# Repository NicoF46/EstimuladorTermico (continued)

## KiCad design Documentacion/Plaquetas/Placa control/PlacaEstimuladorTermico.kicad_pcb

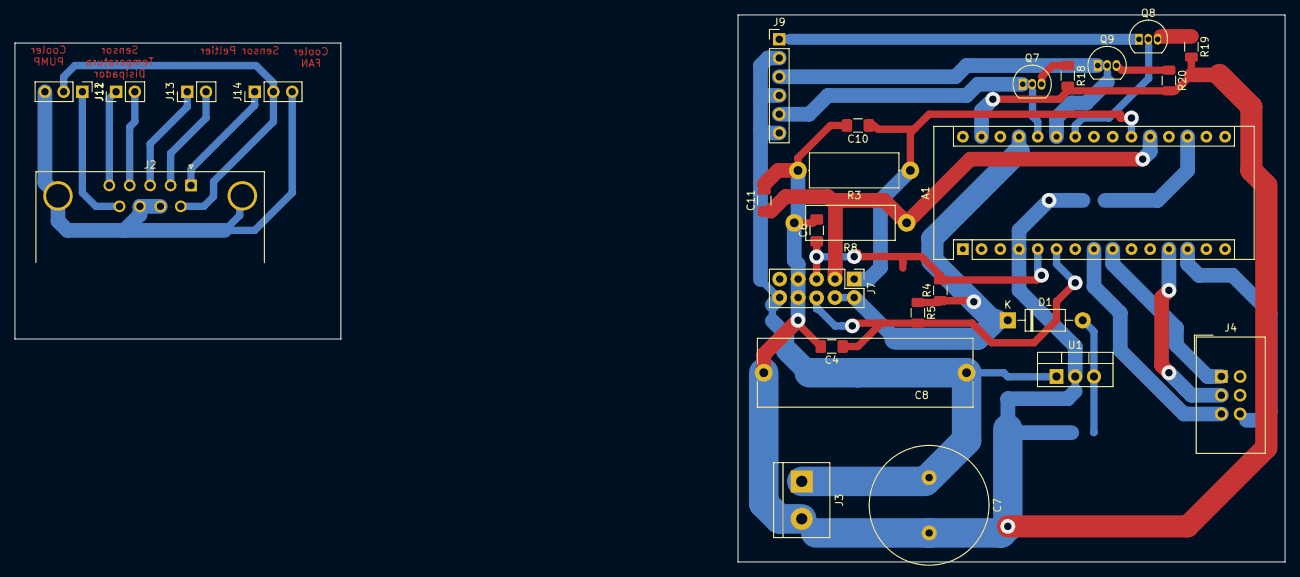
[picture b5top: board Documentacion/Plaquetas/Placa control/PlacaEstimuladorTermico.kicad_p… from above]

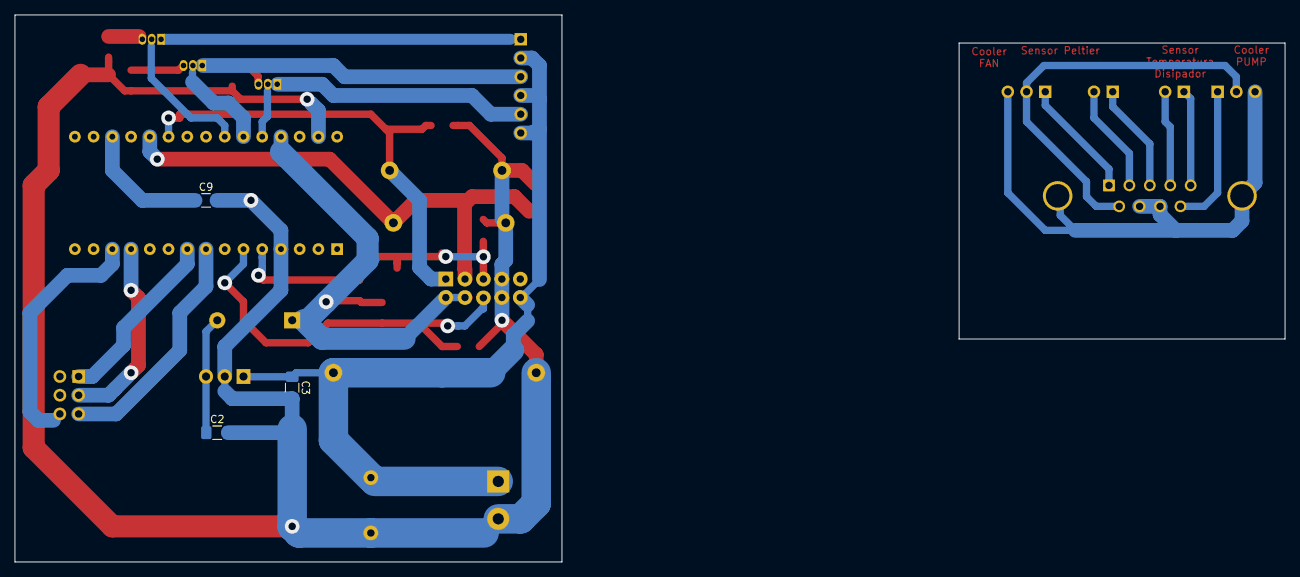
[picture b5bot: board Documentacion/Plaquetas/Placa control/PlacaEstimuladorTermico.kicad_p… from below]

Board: 2 copper layers, 74.2 x 74.2 mm, 31 parts (3 on the bottom side), 30 nets.

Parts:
A1: Arduino_Nano_v3.x; Arduino_Nano
C2, C9: 100n; C_1206_3216Metric_Pad1.42x1.75mm_HandSolder
C3: 330n; C_1206_3216Metric_Pad1.42x1.75mm_HandSolder
C4, C6: 2.2n; C_1206_3216Metric_Pad1.42x1.75mm_HandSolder
C7: 4700u; C_Radial_D16.0mm_H25.0mm_P7.50mm
C8: 4.7u; C_Rect_L29.0mm_W9.1mm_P27.50mm_MKT
C10, C11: 4.7n; C_1206_3216Metric_Pad1.42x1.75mm_HandSolder
D1: 1N4002; D_DO-41_SOD81_P10.16mm_Horizontal
J2: DB9_Female_MountingHoles; DSUB-9_Female_Horizontal_P2.77x2.84mm_EdgePinOffset7.70mm_H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
J3: Screw_Terminal_01x02; TerminalBlock_bornier-2_P5.08mm
J4: Conn_01x06_Male; IDC-Header_2x03_P2.54mm_Vertical
J7: Conn_02x05_Counter_Clockwise; PinHeader_2x05_P2.54mm_VerticalNico
J9: Conn_01x06_Male; PinHeader_1x06_P2.54mm_Vertical
J11, J14: Conn_01x03_Male; PinHeader_1x03_P2.54mm_Vertical
J12, J13: Conn_01x02_Male; PinHeader_1x02_P2.54mm_Vertical
Q7, Q8, Q9: BC548; TO-92_Inline
R3, R8: 10k; R_Axial_DIN0414_L11.9mm_D4.5mm_P15.24mm_Horizontal
R4, R5: 10k; R_1206_3216Metric
R18, R19, R20: 220; R_1206_3216Metric
U1: LM7805_TO220; TO-220-3_Vertical

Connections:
unnamed: A1.18, C9.1
unnamed: C2.1, D1.2, U1.3
unnamed: J9.1, Q8.1
unnamed: J9.3, Q9.1
unnamed: J9.5, Q7.1
unnamed: Q7.3, R18.1
unnamed: Q8.3, R19.1
unnamed: Q9.3, R20.1
PIN-CAUTION-LED-YELLOW: A1.25, Q9.2
PIN-READY-LED-GREEN: A1.24, Q8.2
PIN-WARNING-LED-RED: A1.26, Q7.2
PIN_SENSOR_TEMPERATURA_1: A1.20, C11.1, J7.2, R8.1
PIN_SENSOR_TEMPERATURA_2: A1.21, C10.1, J7.1, R3.1
PMOS_CALOR: A1.9, J4.1
PMOS_FRIO: A1.8, J4.5
PWM_CALOR: A1.12, J4.3
PWM_FRIO: A1.13, J4.6
REF_5: A1.27, D1.1, J7.9, J7.10, R4.1, R5.1
SENSOR_FAN: A1.6, C4.1, J7.8, R5.2
SENSOR_PUMP: A1.5, C6.1, J7.3, R4.2
VCC: C3.1, C7.1, C8.1, J3.1, J7.6, J9.2, J9.4, J9.6, U1.1
fan_1C: J2.6, J11.2, J14.2
fan_2: A1.4, A1.29, C2.2, C3.2, C4.2, C6.2, C7.2, C8.2, C9.2, C10.2, C11.2, J3.2, J7.4, J7.7, R3.2, R8.2, R18.2, R19.2, R20.2, U1.2
fan_2C: J2.7, J2.8, J11.3, J14.3
fan_sensor_C: J2.1, J14.1
pump_sensor_C: J2.9, J11.1
term_1_1C: J2.3, J13.1
term_1_2C: J2.2, J13.2
term_2_1C: J2.5, J12.1
term_2_2C: J2.4, J12.2

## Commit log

2019-04-15 Agrego carpeta para almacenar informacion util del peltier y un par de documentos en la misma
2019-04-15 Modifico Documentacion
2019-04-15 Agrego resumen de los umbrales de dolor y experimento de la mano plastica
2019-04-15 Cambio archivo a la carpeta correcta
2019-04-16 Agrego datasheet tec1-12715
2019-04-19 Agrego el codigo para sensar temperatura con el fabuloso termistor de mati
2019-04-20 quick example of how to plot real time data in python
2019-04-20 created a class Plotter to plot live data
2019-04-25 PWM y cambio a divisor resistivo
    Hecho el 24/04 en el LABI. Se cambio de medicion con puente de wheatstone a divisor resistivo con salida sobre resistencia fija.
    PWM en pin 6 controla la tension de gate del MOSFET
2019-05-07 Agrego documentacion
2019-05-08 added an autoscale option for the plotter
2019-05-10 finished the devices's client side in python
2019-05-10 Create LICENSE
2019-05-14 added a new csv with data
2019-05-14 added a csv_plotter
2019-05-14 Calculo del modelo térmico del Peltier
    Se agrego la documentación en la cual se basaron los cálculos para obtener el modelo térmico del Peltier junto con el código utilizado para obtener los parámetros.
2019-05-14 now the device transmit the pwm
2019-05-14 deleted senartemperaturacontermistor
2019-05-14 added a .gitignore file to ignore .pyc files
2019-05-14 deleted sensartemperaturacontermistor folder
2019-05-15 another test of the PID feedback
2019-05-15 Corrijo un bug
2019-05-15 Agrego los modos para que enfrie o caliente segun la referencia
2019-05-15 calibrated the pid
2019-05-17 Add files via upload
    archivo final miercoles 15/5
2019-05-19 started to modify the new circuit's firmware
2019-05-20 added a new mode selector
2019-05-20 changed the PID controller
2019-05-21 Now the device receive the temperature via serial interface
2019-05-21 updated requirements.txt
2019-05-22 started a cmd interface to send messages to the device
2019-05-22 added cmd package to requirements.txt
2019-05-22 finished the first version of the device
2019-08-20 fixing a bug when detecting the usb port
2019-08-27 Updated peltier model estimation
2019-09-06 Subo las simulaciones del informe correspondientes al circuito de control, me faltan las simulaciones del H bridge, la simulacion asi como la configure tarda un toque.
2019-09-06 Minor changes to peltier model estimation
2019-09-06 Agrego las 2 fotos
2019-09-29 Subo codigo del control en C
2019-10-01 Agrego jpg con el circuito de la placa de mati, cambie las resistencias de los mos de 100k a 10k, agregue el filtro LC y diodos flyback
2019-10-01 Simulación Circuito Protección
2019-10-02 Arreglo la transmision serie del arduino a la pc, me falta arreglar la de pc a arduino
2019-10-03 Resolvi el problema de la comunicacion, probe el codigo del pid funciona, tengo que ajustarlo y hacer la funcion de calibracion, dato a color el disipador con el filtro no calienta ni enfria como ant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
2019-10-05 Agrego el codigo para la calibracion
2019-10-14 Agrego el esquematico de la version 2 de la placa, me faltan algunos valores de resistencias y protecciones
2019-10-14 Agrego la resistencia en los mos
2019-10-17 Agrego el esquematico en png para mostrarlo hoy
2019-10-20 Deleting unnecesary files
2019-10-20 deleting .o and .hex files
2019-10-22 I selected the commercial components values and added to the schematic, I dont know if all the lines are connected correctly so please someone revise
2019-10-30 Add files via upload
    Actualizacion de esquematico: agregada proteccion de bateria
2019-11-01 Adding indicator lights and values to components
2019-11-02 I add all the footprints, the position of the high power mosfets is in acordance with a heatsink that I had
2019-11-04 I designed the pcb, it was my first try so please check every wire
2019-11-07 Add battery level to scheme, protection circuit correction & arranging
2019-11-07 add relay module symbol and footprint, modify mcp1407 symbol
    plus updates of these on the schematic
2019-11-09 solve kicad library issues
2019-11-28 Change pins of pwm and on off, adjusting pins in code to correct the problem
2019-12-03 DB9 board for peltier case
2019-12-03 DB9 board with bigger pads
2019-12-08 Correction of all the errors in the pcb
2019-12-09 Correction of pwm pins
2019-12-15 Modification of the main board, add of leds circuit and db9 board
2019-12-15 Add holes to the board
2019-12-15 Modifications in the schematic
2020-01-01 simplification of the dissipator temperature measurement circuit and simplification of code
2020-01-01 Add fuse and 7805 to supply the arduino nano
2020-01-05 Divide pcb in sectors based in functionality
2020-01-19 Updating firmware
2020-01-22 Creation of power pcb
2020-01-23 Possible layout
    Needs some rearenging.
    Added kiCAD backup files to ignore list
2020-01-24 Power PCB Routed
2020-01-29 Power PCB revised
    Minor changes in size and vias
2020-02-02 Power PCB footprints updated
2020-02-03 Power PCB retraced routes for new footprints
2020-02-03 Power PCB complete route retracing
2020-02-05 Power PCB revision - via size, signal connector pos and front pow traces
2020-02-07 Power PCB changed logic connector, widened traces, added mounting holes
2020-02-29 removing cache files
2020-02-29 removing kickad tables files
2020-02-29 removing kickad table files
2020-02-29 updating gitignore file
2020-03-01 Modifico el codigo para sintonizar el pid
2020-03-04 Protection PCB creation
    Needs choosing inverse polarity connection protection method
2020-03-05 Protection circuit on routed one sided 100x50mm board
    Relay outside board
    Possible improvements:
    - J3 moved left, decreases tracks length
    - U1 moved down, decreases tracks length, increases spacing between components
2020-03-07 removing *table files from gitignore
2020-03-18 Protection PCB footprint update, adjustable zenner ref set, pad resize
2020-03-20 Protection PCB widen tracks, connected unused opamp
    This is the final version. It was printed and etched
2020-03-31 Add control schematic
2020-05-10 changes in the schematic and pcb
2020-05-11 Addition of connetors on scheema and PCB
2020-05-11 PR requested schematic changes + removal of fan power supply conectors
    Fan power supply is going to be addressed by the protection circuit board
2020-05-11 git ignore
2020-05-13 Addition of buzzer, display and cold led
    Added a missing footprint to project
2020-05-14 Added fan supply circuitry, merged two 5v thermistor pin in one
2020-05-18 Added capacitor to buzzer transistor's base, changed 7805 diode side
    changed connector wire order,
    added proof of concept layout for single sided board,
    removed outdated and cache files
2020-05-19 Possible route design, swapped display connector pins
2020-05-19 Changed pump and fan sensor pins, routed accordingly, shrunk board size
2020-05-27 Possible design, swapped sda and scl connector pins
2020-05-27 changed buzzer to common collector mode
2020-06-06 Actualizacion del firmware por cambio en el hardware
2020-06-19 change pid and add commands for serial to work with flask
2020-07-04 adding multiple lines in a single plot
2020-07-04 updating data_acquisition script with the live_plot update
2020-07-06 upload changes calibration and pid
2020-07-12 Reorganising file composition
2020-07-17 adding the status library
2020-07-18 updating firmware with the new changes
2020-07-18 fixin a bad identation
2020-07-18 spliting status library into status and error library since some status and the NO_ERROR error state are compatibles
2020-07-18 adding a command to set errors
2020-07-18 Adding a code format option to the Makefile
2020-07-18 formatting code
2020-07-18 Fixing a missing path in the clean rule
2020-07-18 adding a script to setup the packages needed for development
2020-07-18 Installing a virtual environment with the python needs in the set up script
2020-07-19 Reading the temperature asynchronously
2020-07-28 adding a command to get the current pwm
2020-07-29 fixing a bug with the temperature used by reference
2020-08-08 Adding flags for each error
2020-08-10 code refactoring
2020-08-13 Adding a parity error check for usart transmision
2020-08-13 Adding sound alarm when an error is set
2020-08-17 Updating makefile to generate pygen files
2020-08-17 first aproach to a command generator based on a json file
2020-08-17 Autogenerating functions to red and transmit commands frames
2020-08-23 Fiing a bug with the function read_chung in commander.py
2020-08-30 Fixing a bug in Makefile. It rebuild the project if there are changes in .json files
2020-08-31 Removing .gen.c files with make clean
2020-08-31 adding a temperature module
2020-08-31 adding a power_board library
2020-08-31 declaring as const input variables
2020-08-31 removing old files
2020-09-01 removing duplicated variable in Makefile
2020-09-07 Refactoring controller functions and adding documentation to some funcionts
2020-09-07 updating data link
2020-09-07 Adding measures to compare thermistors in different locations
2020-09-10 adding a command that return the average temperature
2020-09-13 Adding stop command and fixig a bug where the live plot windows was always on top
2020-09-13 adding errors commands
2020-09-13 Swaping leds ports for the new board
2020-09-20 adding a starting routine to test leds and the buzzer
2020-09-20 Reducing the test duration
2020-09-20 Reducing even more the test duration
2020-10-13 Adding a keep alive that resets on each temperature_read command call
2020-10-16 Finishing the keep alive implementation
2020-10-17 first aproach to an error checker. Tachometer is not checked still
2020-11-11 checking errors in the main loop
2020-11-23 Checking if fan rpm are lower than half of its standard value
2020-11-24 Fixing comments
2020-11-24 Making the controller set the pwm to zero if the differece between temperature reference and the actual temp is higher than 13
2020-11-24 Setting reached status
2020-11-30 Setting a new flag to avoid the fan_rpm_error when the power is off
